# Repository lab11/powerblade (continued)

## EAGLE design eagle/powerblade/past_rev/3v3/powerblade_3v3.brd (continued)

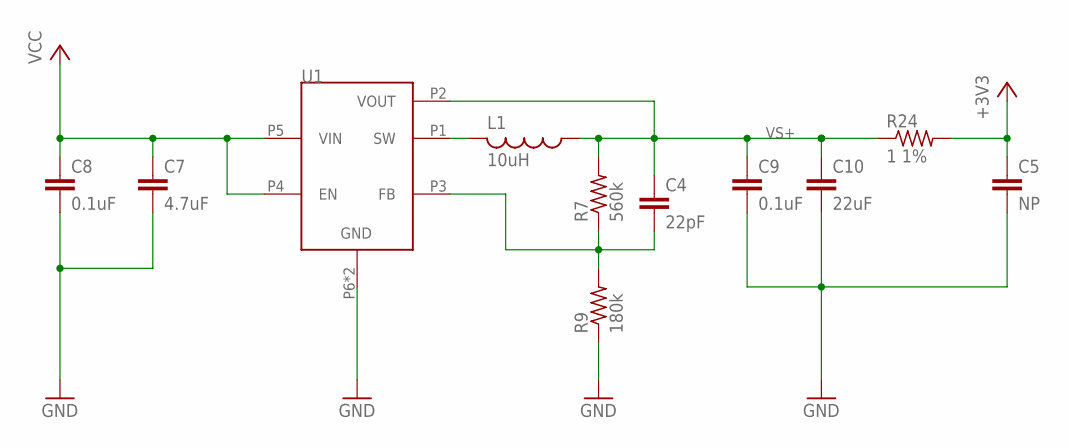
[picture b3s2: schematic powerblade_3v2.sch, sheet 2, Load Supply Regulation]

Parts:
C4: 22pF; C0402; DIGIKEY 445-1239-1-ND
C5: NP; C0603_TN; DIGIKEY NP
C7: 4.7uF; C0402; DIGIKEY 445-8023-1-ND
C8: 0.1uF; C0402; DIGIKEY 445-4952-1-ND
C9: 0.1uF; C0402_SM; DIGIKEY 445-4952-1-ND
C10: 22uF; C0603_SM; DIGIKEY 445-9077-1-ND
L1: 10uH; L0805; DIGIKEY 490-4990-1-ND
R7: 560k; R0402; DIGIKEY P560KLCT-ND
R9: 180k; R0402; DIGIKEY P180KLCT-ND
R24: 1 1%; R0603_SM; DIGIKEY P1.0AJCT-ND
U1: TPS62122; WDFN-6

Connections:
+3V3: C5.1, R24.2; also elsewhere on the board
unnamed: L1.2, U1.P1 (SW)
unnamed: C4.2, R7.1, R9.2, U1.P3 (FB)
VCC: C7.1, C8.1, U1.P4 (EN), U1.P5 (VIN); also elsewhere on the board
VS+: C4.1, C9.1, C10.1, L1.1, R7.2, R24.1, U1.P2 (VOUT); also elsewhere on the board

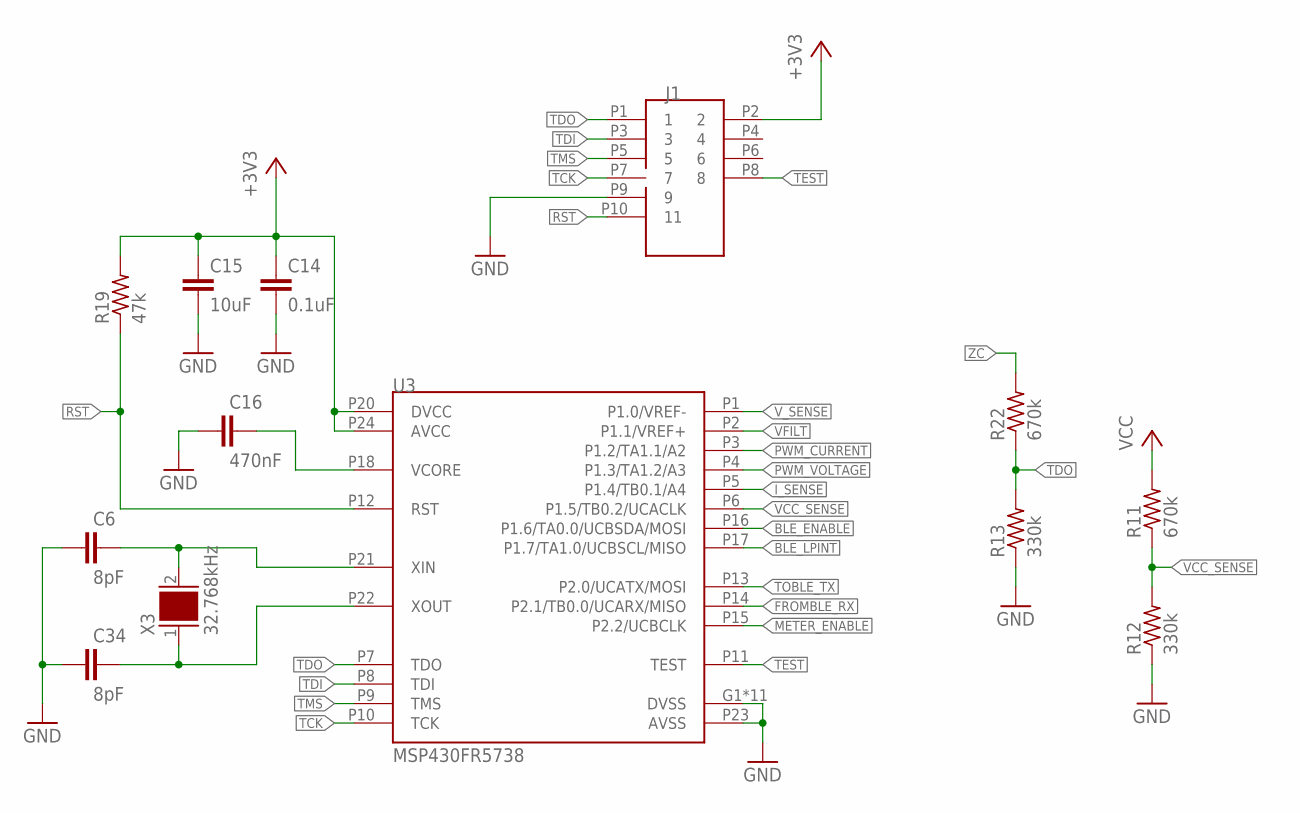
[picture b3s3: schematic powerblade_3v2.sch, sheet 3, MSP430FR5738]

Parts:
C6, C34: 8pF; C0402; DIGIKEY 445-4890-1-ND
C14: 0.1uF; C0402; DIGIKEY 445-4952-1-ND
C15: 10uF; C0603_SM; DIGIKEY 445-6853-1-ND
C16: 470nF; C0402; DIGIKEY 445-4989-1-ND
J1: JTAG_14PIN_IDC-ND; TC2050-IDC-NL-430-ND; DIGIKEY NP
R11, R22: 670k; R0402; DIGIKEY P665KLCT-ND
R12, R13: 330k; R0402; DIGIKEY P330KLCT-ND
R19: 47k; R0402; DIGIKEY P47KJCT-ND
U3: MSP430FR5738; VQFN-24
X3: 32.768kHz; 0805; DIGIKEY 535-12373-1-ND

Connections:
+3V3: C14.1, C15.1, J1.P2 (2), R19.2, U3.P20 (DVCC), U3.P24 (AVCC); also elsewhere on the board
BLE_ENABLE: U3.P16 (P1.6/TA0.0/UCBSDA/MOSI); also elsewhere on the board
BLE_LPINT: U3.P17 (P1.7/TA1.0/UCBSCL/MISO); also elsewhere on the board
FROMBLE_RX: U3.P14 (P2.1/TB0.0/UCARX/MISO); also elsewhere on the board
METER_ENABLE: U3.P15 (P2.2/UCBCLK); also elsewhere on the board
unnamed: C34.2, U3.P22 (XOUT), X3.1
unnamed: C16.2, U3.P18 (VCORE)
unnamed: C6.2, U3.P21 (XIN), X3.2
PWM_CURRENT: U3.P3 (P1.2/TA1.1/A2); also elsewhere on the board
PWM_VOLTAGE: U3.P4 (P1.3/TA1.2/A3); also elsewhere on the board
RST: J1.P10 (11), R19.1, U3.P12 (RST)
TCK: J1.P7 (7), U3.P10 (TCK)
TDI: J1.P3 (3), U3.P8 (TDI)
TDO: J1.P1 (1), R13.2, R22.1, U3.P7 (TDO)
TEST: J1.P8 (8), U3.P11 (TEST)
TMS: J1.P5 (5), U3.P9 (TMS)
TOBLE_TX: U3.P13 (P2.0/UCATX/MOSI); also elsewhere on the board
VCC: R11.2; also elsewhere on the board
VCC_SENSE: R11.1, R12.2, U3.P6 (P1.5/TB0.2/UCACLK)
VFILT: U3.P2 (P1.1/VREF+); also elsewhere on the board
ZC: R22.2; also elsewhere on the board

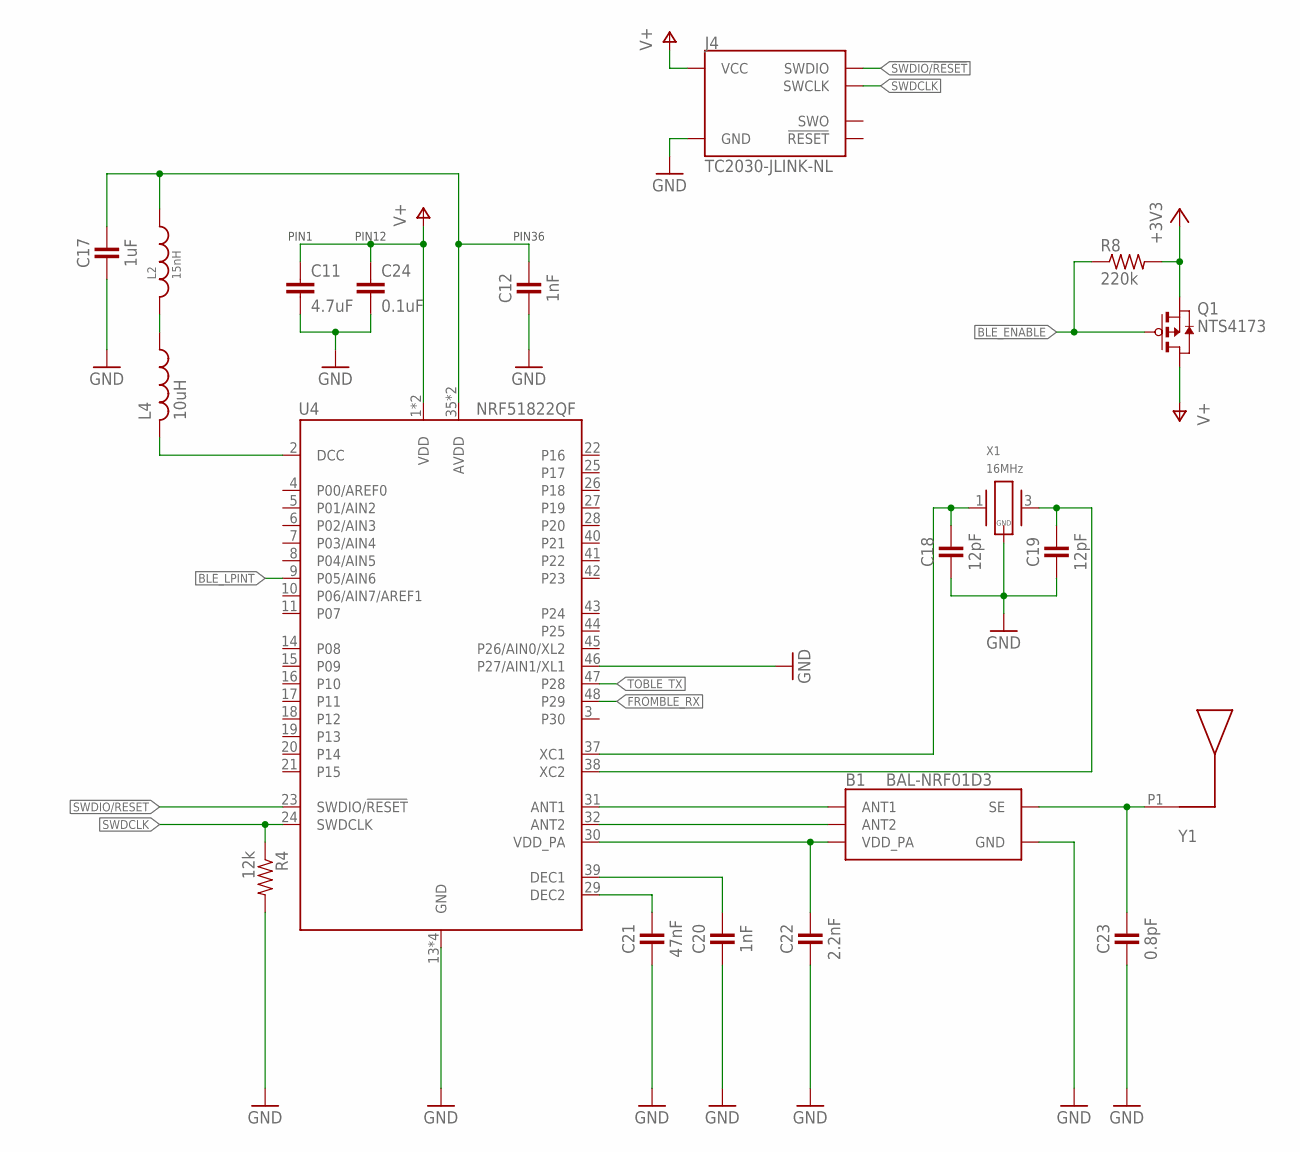
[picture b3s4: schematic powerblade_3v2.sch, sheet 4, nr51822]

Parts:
B1: BAL-NRF01D3
C11: 4.7uF; C0402; DIGIKEY 445-5947-1-ND
C12, C20: 1nF; 0402_CAP; DIGIKEY 490-1303-1-ND
C17: 1uF; 0402_CAP; DIGIKEY 1276-1513-1-ND
C18, C19: 12pF; 0402_CAP; DIGIKEY 490-6197-1-ND
C21: 47nF; 0402_CAP; DIGIKEY 445-1264-1-ND
C22: 2.2nF; 0402_CAP; DIGIKEY 490-5419-1-ND
C23: 0.8pF; 0402_CAP; DIGIKEY 490-6269-1-ND
C24: 0.1uF; C0402; DIGIKEY 445-4952-1-ND
J4: TC2030-JLINK-NL; TC2030-IDC-NL; DIGIKEY NP
L2: 15nH; 0402_CAP; DIGIKEY 587-1521-1-ND
L4: 10uH; C0603_TN; DIGIKEY 490-4025-1-ND
Q1: NTS4173; SC-70-3
R4: 12k; 0402_RES; DIGIKEY RHM12.0KCDCT-ND
R8: 220k; R0402_SM; DIGIKEY P220KJCT-ND
U4: NRF51822QF; QFN-48-6MM
X1: 16MHz; TXC-8Y; DIGIKEY 887-2003-1-ND
Y1: UREACH_XTEND

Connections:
+3V3: Q1.P2 (S), R8.2; also elsewhere on the board
AVDD: C12.1, C17.1, L2.1, U4.35 (AVDD), U4.36 (AVDD)
BLE_ENABLE: Q1.P1 (G), R8.1; also elsewhere on the board
BLE_LPINT: U4.9 (P05/AIN6); also elsewhere on the board
DCC: L4.2, U4.2 (DCC)
FROMBLE_RX: U4.48 (P29); also elsewhere on the board
unnamed: B1.SE, C23.1, Y1.P1
unnamed: B1.ANT1, U4.31 (ANT1)
unnamed: B1.ANT2, U4.32 (ANT2)
unnamed: L2.2, L4.1
unnamed: C18.1, U4.37 (XC1), X1.1
unnamed: C19.1, U4.38 (XC2), X1.3 (2)
unnamed: C20.1, U4.39 (DEC1)
unnamed: C21.1, U4.29 (DEC2)
SWDCLK: J4.4 (SWCLK), R4.1, U4.24 (SWDCLK)
SWDIO/!RESET: J4.2 (SWDIO), U4.23 (SWDIO/!RESET)
TOBLE_TX: U4.47 (P28); also elsewhere on the board
V+: C11.1, C24.1, J4.1 (VCC), Q1.P3 (D), U4.1 (VDD), U4.12 (VDD)
VDD_PA: B1.VCC (VDD_PA), C22.1, U4.30 (VDD_PA)

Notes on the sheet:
PIN12
PIN1
PIN36

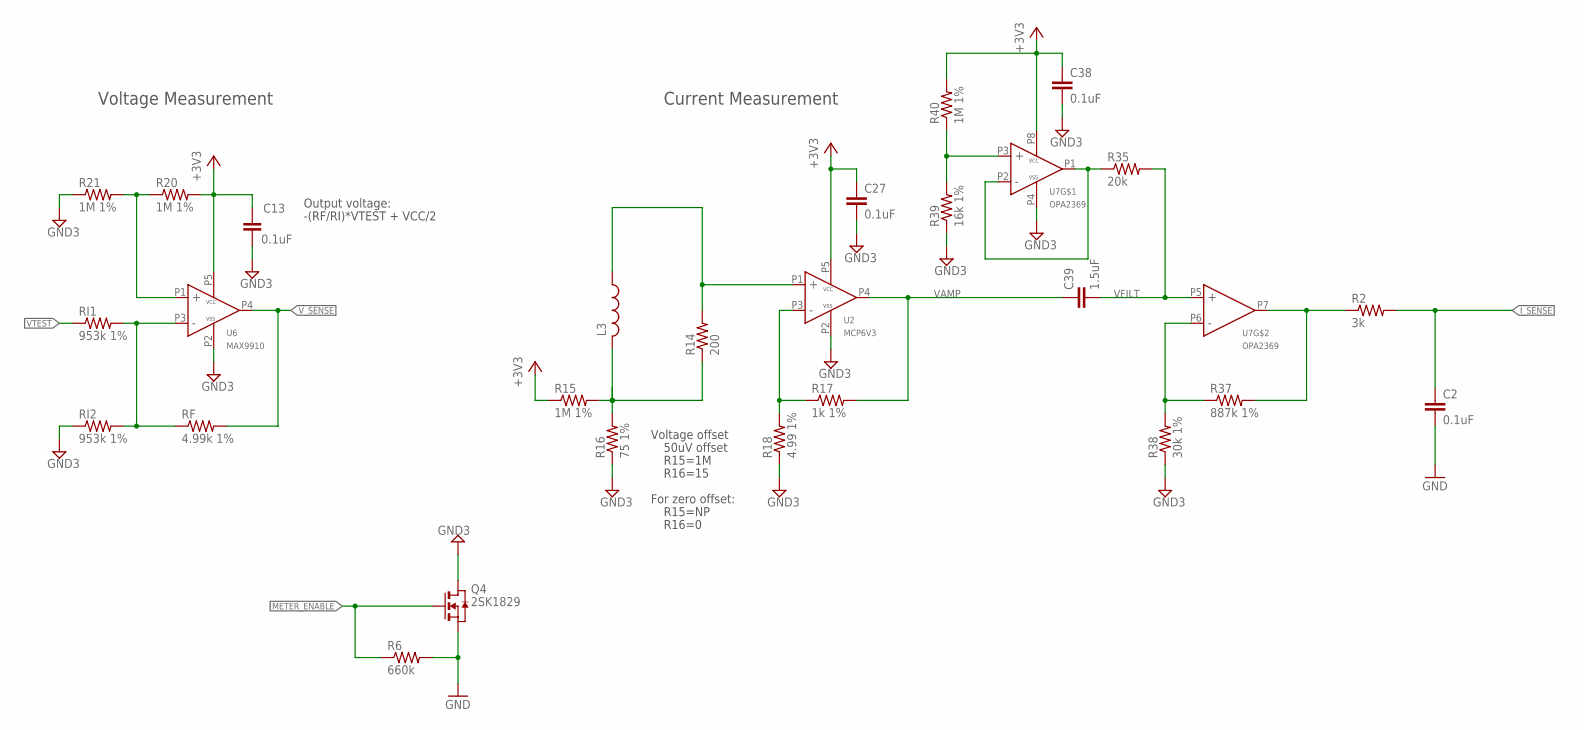
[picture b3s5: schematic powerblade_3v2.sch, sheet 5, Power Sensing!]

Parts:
C2: 0.1uF; C0402; DIGIKEY 490-10777-1-ND
C13: 0.1uF; 0402_CAP; DIGIKEY 445-4952-1-ND
C27, C38: 0.1uF; C0402; DIGIKEY 445-4952-1-ND
C39: 1.5uF; C0402; DIGIKEY 445-13815-1-ND
L3: L-USL0805; L0805; DIGIKEY 732-3452-1-ND
Q4: 2SK1829; SC-70-3
R2: 3k; R0402_SM; DIGIKEY P3.00KLCT-ND
R6: 660k; R0402; DIGIKEY P665KLCT-ND
R14: 200; R0402; DIGIKEY P200LCT-ND
R15, R20, R40: 1M 1%; R0402; DIGIKEY P1.00MLCT-ND
R16: 75 1%; R0402; DIGIKEY P75.0LCT-ND
R17: 1k 1%; R0402; DIGIKEY P1.00KLCT-ND
R18: 4.99 1%; R0402; DIGIKEY RMCF0402FT4R99CT-ND
R21: 1M 1%; R0402_SM; DIGIKEY P1.00MLCT-ND
R35: 20k; R0402; DIGIKEY P20.0KLCT-ND
R37: 887k 1%; R0402; DIGIKEY P887KLCT-ND
R38: 30k 1%; R0402; DIGIKEY P30.0KLCT-ND
R39: 16k 1%; R0402; DIGIKEY P16.0KLCT-ND
RF: 4.99k 1%; R0402; DIGIKEY P4.99KLCT-ND
RI1, RI2: 953k 1%; R0402; DIGIKEY P953KLCT-ND
U2: MCP6V3; SC70-5; DIGIKEY 296-19547-1-ND
U6: MAX9910; SC70-5; DIGIKEY 296-25252-1-ND
U7: OPA2369; SOT-23-8

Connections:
+3V3: C13.1, C27.1, C38.1, R15.1, R20.2, R40.2, U2.P5 (VCC), U6.P5 (VCC), U7.P8 (VCC); also elsewhere on the board
METER_ENABLE: Q4.P1 (G), R6.1; also elsewhere on the board
unnamed: R2.1, R37.2, U7.P7 (OUT)
unnamed 20: L3.2, R14.1, R15.2, R16.2; also elsewhere on the board
unnamed: L3.1, R14.2, U2.P1 (IN+)
unnamed: R20.1, R21.2, U6.P1 (IN+)
unnamed: RF.1, RI1.2, RI2.2, U6.P3 (IN-)
unnamed 25: R17.1, R18.2, U2.P3 (IN-); also elsewhere on the board
unnamed: R37.1, R38.2, U7.P6 (IN-)
unnamed: R35.1, U7.P1 (OUT), U7.P2 (IN-)
unnamed: R39.2, R40.1, U7.P3 (IN+)
VAMP: C39.1, R17.2, U2.P4 (OUT)
VFILT: C39.2, R35.2, U7.P5 (IN+); also elsewhere on the board
VTEST: RI1.1; also elsewhere on the board

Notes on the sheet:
Voltage offset
50uV offset
For zero offset:
R15=NP
R16=0
Current Measurement
Voltage Measurement
Output voltage:
-(RF/RI)*VTEST + VCC/2
R15=1M
R16=15

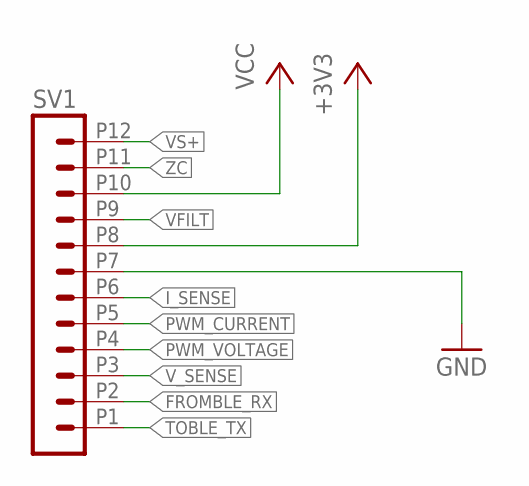
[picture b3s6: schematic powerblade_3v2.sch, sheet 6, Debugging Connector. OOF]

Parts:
SV1: MA12-11M27; MA12-1_1MM27; DIGIKEY S9014E-12-ND

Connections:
+3V3: SV1.P8 (8); also elsewhere on the board
FROMBLE_RX: SV1.P2 (2); also elsewhere on the board
PWM_CURRENT: SV1.P5 (5); also elsewhere on the board
PWM_VOLTAGE: SV1.P4 (4); also elsewhere on the board
TOBLE_TX: SV1.P1 (1); also elsewhere on the board
VCC: SV1.P10 (10); also elsewhere on the board
VFILT: SV1.P9 (9); also elsewhere on the board
VS+: SV1.P12 (12); also elsewhere on the board
ZC: SV1.P11 (11); also elsewhere on the board

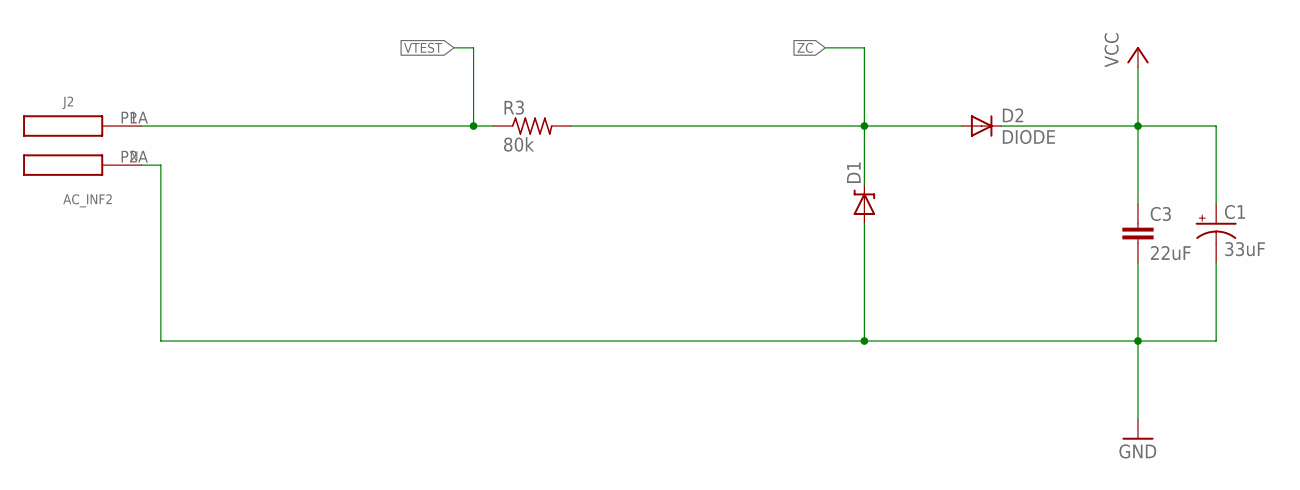
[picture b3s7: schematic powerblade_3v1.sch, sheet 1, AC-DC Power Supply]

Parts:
C1: 33uF; CPOL0805_SM; DIGIKEY 478-8650-1-ND
C3: 22uF; C0603_SM; DIGIKEY 445-9077-1-ND
D1: ZENERBZT52; BZT52; DIGIKEY BZT52C10T-7DICT-ND
D2: DIODE; BAS521
J2: AC_INF2; AC3_F2; DIGIKEY NP
R3: 80k; R1210; DIGIKEY P80.6KAACT-ND

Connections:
VCC: C1.+, C3.1, D2.C; also elsewhere on the board
VTEST: J2.P1A, R3.1; also elsewhere on the board
ZC: D1.C, D2.A, R3.2; also elsewhere on the board

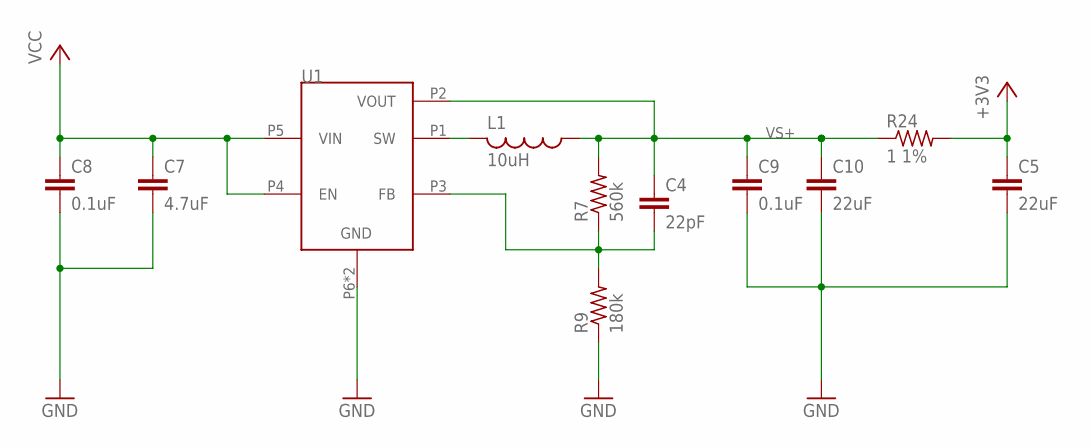
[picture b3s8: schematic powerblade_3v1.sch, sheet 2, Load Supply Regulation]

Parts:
C4: 22pF; C0402_SM; DIGIKEY 445-1239-1-ND
C5: 22uF; C0603_TN; DIGIKEY 445-9077-1-ND
C7: 4.7uF; C0402_SM; DIGIKEY 445-8023-1-ND
C8, C9: 0.1uF; C0402_SM; DIGIKEY 445-4952-1-ND
C10: 22uF; C0603_SM; DIGIKEY 445-9077-1-ND
L1: 10uH; L0805; DIGIKEY 490-4990-1-ND
R7: 560k; R0402_SM; DIGIKEY P560KLCT-ND
R9: 180k; R0402_SM; DIGIKEY P180KLCT-ND
R24: 1 1%; R0603_SM; DIGIKEY P1.0AJCT-ND
U1: TPS62122; WDFN-6

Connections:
+3V3: C5.1, R24.2; also elsewhere on the board
unnamed: L1.2, U1.P1 (SW)
unnamed: C4.2, R7.1, R9.2, U1.P3 (FB)
VCC: C7.1, C8.1, U1.P4 (EN), U1.P5 (VIN); also elsewhere on the board
VS+: C4.1, C9.1, C10.1, L1.1, R7.2, R24.1, U1.P2 (VOUT); also elsewhere on the board

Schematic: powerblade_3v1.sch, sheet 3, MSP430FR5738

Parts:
C6, C34: 8pF; C0402_SM; DIGIKEY 445-4890-1-ND
C14: 0.1uF; C0402_SM; DIGIKEY 445-4952-1-ND
C15: 10uF; C0603_SM; DIGIKEY 445-6853-1-ND
C16: 470nF; C0402_SM; DIGIKEY 445-4989-1-ND
J1: JTAG_14PIN_IDC-ND; TC2050-IDC-NL-430-ND; DIGIKEY NP
R11, R22: 670k; R0402_SM; DIGIKEY P665KLCT-ND
R12, R13: 330k; R0402_SM; DIGIKEY P330KLCT-ND
R19: 47k; R0402_SM; DIGIKEY P47KJCT-ND
U3: MSP430FR5738; VQFN-24
X3: 32.768kHz; 0805; DIGIKEY 535-12373-1-ND

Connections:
+3V3: C14.1, C15.1, J1.P2 (2), R19.2, U3.P20 (DVCC), U3.P24 (AVCC); also elsewhere on the board
BLE_ENABLE: U3.P16 (P1.6/TA0.0/UCBSDA/MOSI); also elsewhere on the board
BLE_LPINT: U3.P17 (P1.7/TA1.0/UCBSCL/MISO); also elsewhere on the board
FROMBLE_RX: U3.P14 (P2.1/TB0.0/UCARX/MISO); also elsewhere on the board
METER_ENABLE: U3.P15 (P2.2/UCBCLK); also elsewhere on the board
unnamed: C34.2, U3.P22 (XOUT), X3.1
unnamed: C16.2, U3.P18 (VCORE)
unnamed: C6.2, U3.P21 (XIN), X3.2
PWM_CURRENT: U3.P3 (P1.2/TA1.1/A2); also elsewhere on the board
PWM_VOLTAGE: U3.P4 (P1.3/TA1.2/A3); also elsewhere on the board
RST: J1.P10 (11), R19.1, U3.P12 (RST)
TCK: J1.P7 (7), U3.P10 (TCK)
TDI: J1.P3 (3), U3.P8 (TDI)
TDO: J1.P1 (1), R13.2, R22.1, U3.P7 (TDO)
TEST: J1.P8 (8), U3.P11 (TEST)
TMS: J1.P5 (5), U3.P9 (TMS)
TOBLE_TX: U3.P13 (P2.0/UCATX/MOSI); also elsewhere on the board
VCC: R11.2; also elsewhere on the board
VCC_SENSE: R11.1, R12.2, U3.P6 (P1.5/TB0.2/UCACLK)
VFILT: U3.P2 (P1.1/VREF+); also elsewhere on the board
ZC: R22.2; also elsewhere on the board

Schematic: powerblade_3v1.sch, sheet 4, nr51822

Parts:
B1: BAL-NRF01D3
C11: 4.7uF; C0402_SM; DIGIKEY 445-5947-1-ND
C12, C20: 1nF; 0402_CAP; DIGIKEY 490-1303-1-ND
C17: 1uF; 0402_CAP; DIGIKEY 1276-1513-1-ND
C18, C19: 12pF; 0402_CAP; DIGIKEY 490-6197-1-ND
C21: 47nF; 0402_CAP; DIGIKEY 445-1264-1-ND
C22: 2.2nF; 0402_CAP; DIGIKEY 490-5419-1-ND
C23: 0.8pF; 0402_CAP; DIGIKEY 490-6269-1-ND
C24: 0.1uF; C0402_SM; DIGIKEY 445-4952-1-ND
J4: TC2030-JLINK-NL; TC2030-IDC-NL; DIGIKEY NP
L2: 15nH; 0402_CAP; DIGIKEY 587-1521-1-ND
L4: 10uH; C0603_TN; DIGIKEY 490-4025-1-ND
Q1: NTS4173; SC-70-3
R4: 12k; 0402_RES; DIGIKEY RHM12.0KCDCT-ND
R8: 220k; R0402_SM; DIGIKEY P220KJCT-ND
U4: NRF51822QF; QFN-48-6MM
X1: 16MHz; TXC-8Y; DIGIKEY 887-2003-1-ND
Y1: UREACH_XTEND

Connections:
+3V3: Q1.P2 (S), R8.2; also elsewhere on the board
AVDD: C12.1, C17.1, L2.1, U4.35 (AVDD), U4.36 (AVDD)
BLE_ENABLE: Q1.P1 (G), R8.1; also elsewhere on the board
BLE_LPINT: U4.9 (P05/AIN6); also elsewhere on the board
DCC: L4.2, U4.2 (DCC)
FROMBLE_RX: U4.48 (P29); also elsewhere on the board
unnamed: B1.SE, C23.1, Y1.P1
unnamed: B1.ANT1, U4.31 (ANT1)
unnamed: B1.ANT2, U4.32 (ANT2)
unnamed: L2.2, L4.1
unnamed: C18.1, U4.37 (XC1), X1.1
unnamed: C19.1, U4.38 (XC2), X1.3 (2)
unnamed: C20.1, U4.39 (DEC1)
unnamed: C21.1, U4.29 (DEC2)
SWDCLK: J4.4 (SWCLK), R4.1, U4.24 (SWDCLK)
SWDIO/!RESET: J4.2 (SWDIO), U4.23 (SWDIO/!RESET)
TOBLE_TX: U4.47 (P28); also elsewhere on the board
V+: C11.1, C24.1, J4.1 (VCC), Q1.P3 (D), U4.1 (VDD), U4.12 (VDD)
VDD_PA: B1.VCC (VDD_PA), C22.1, U4.30 (VDD_PA)

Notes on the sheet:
PIN12
PIN1
PIN36

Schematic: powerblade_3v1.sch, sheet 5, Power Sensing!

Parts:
C2: C-EUC0402_SM; C0402_SM
C13: 0.1uF; 0402_CAP; DIGIKEY 445-4952-1-ND
C27, C38: 0.1uF; C0402_SM; DIGIKEY 445-4952-1-ND
C39: 1.5uF; C0402_SM; DIGIKEY 445-13815-1-ND
L3: L-USL0805; L0805; DIGIKEY 732-3452-1-ND
Q4: 2SK1829; SC-70-3
R1: NP; R0402_SM; DIGIKEY NP
R2: R-US_R0402_SM; R0402_SM
R6: 660k; R0402_SM; DIGIKEY P665KLCT-ND
R14: 200; R0402_SM; DIGIKEY P200LCT-ND
R15, R20, R21, R40: 1M 1%; R0402_SM; DIGIKEY P1.00MLCT-ND
R16: 75 1%; R0402_SM; DIGIKEY P75.0LCT-ND
R17: 4.99k 1%; R0402_SM; DIGIKEY P4.99KLCT-ND
R18: 4.99 1%; R0402_SM; DIGIKEY RMCF0402FT4R99CT-ND
R35: 20k; R0402_SM; DIGIKEY P2.00KLCT-ND
R37: 887k 1%; R0402_SM; DIGIKEY P887KLCT-ND
R38: 30k 1%; R0402_SM; DIGIKEY P30.0KLCT-ND
R39: 16k 1%; R0402_SM; DIGIKEY P16.0KLCT-ND
RF: 4.99k 1%; R0402_SM; DIGIKEY P4.99KLCT-ND
RI1, RI2: 953k 1%; R0402_SM; DIGIKEY P953KLCT-ND
U2: MCP6V3; SC70-5; DIGIKEY_POP 296-19547-1-ND
U6: MAX9910; SC70-5; DIGIKEY 296-25252-1-ND
U7: OPA2369; SOT-23-8

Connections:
+3V3: C13.1, C27.1, C38.1, R15.1, R20.2, R40.2, U2.P5 (VCC), U6.P5 (VCC), U7.P8 (VCC); also elsewhere on the board
METER_ENABLE: Q4.P1 (G), R6.1; also elsewhere on the board
unnamed: R2.1, R37.2, U7.P7 (OUT)
unnamed: L3.2, R1.1, R14.1, R15.2, R16.2
unnamed: L3.1, R14.2, U2.P1 (IN+)
unnamed: R20.1, R21.2, U6.P1 (IN+)
unnamed: RF.1, RI1.2, RI2.2, U6.P3 (IN-)
unnamed: R1.2, R17.1, R18.2, U2.P3 (IN-)
unnamed: R37.1, R38.2, U7.P6 (IN-)
unnamed: R35.1, U7.P1 (OUT), U7.P2 (IN-)
unnamed: R39.2, R40.1, U7.P3 (IN+)
VAMP: C39.1, R17.2, U2.P4 (OUT)
VFILT: C39.2, R35.2, U7.P5 (IN+); also elsewhere on the board
VTEST: RI1.1; also elsewhere on the board

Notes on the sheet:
Voltage offset
50uV offset
For zero offset:
R15=NP
R16=0
Current Measurement
Voltage Measurement
Output voltage:
-(RF/RI)*VTEST + VCC/2
R15=1M
R16=15

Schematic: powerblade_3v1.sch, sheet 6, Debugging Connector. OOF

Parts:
SV1: MA12-11M27; MA12-1_1MM27; DIGIKEY S9014E-12-ND

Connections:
+3V3: SV1.P8 (8); also elsewhere on the board
FROMBLE_RX: SV1.P2 (2); also elsewhere on the board
PWM_CURRENT: SV1.P5 (5); also elsewhere on the board
PWM_VOLTAGE: SV1.P4 (4); also elsewhere on the board
TOBLE_TX: SV1.P1 (1); also elsewhere on the board
VCC: SV1.P10 (10); also elsewhere on the board
VFILT: SV1.P9 (9); also elsewhere on the board
VS+: SV1.P12 (12); also elsewhere on the board
ZC: SV1.P11 (11); also elsewhere on the board

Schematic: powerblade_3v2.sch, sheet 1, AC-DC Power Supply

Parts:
C1: 33uF; CPOL0805_SM; DIGIKEY 478-8650-1-ND
C3: 22uF; C0603_SM; DIGIKEY 445-9077-1-ND
D1: ZENERBZT52; BZT52; DIGIKEY BZT52C10T-7DICT-ND
D2: DIODE; BAS521
J2: AC_INF45; AC3_F45; DIGIKEY ED1649-ND
R3: 69.8k; R1210; DIGIKEY P69.8KAACT-ND

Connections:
VCC: C1.+, C3.1, D2.C; also elsewhere on the board
VTEST: J2.PA.3, R3.1; also elsewhere on the board
ZC: D1.C, D2.A, R3.2; also elsewhere on the board

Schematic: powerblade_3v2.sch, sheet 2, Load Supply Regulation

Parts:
C4: 22pF; C0402; DIGIKEY 445-1239-1-ND
C5: NP; C0603_TN; DIGIKEY NP
C7: 4.7uF; C0402; DIGIKEY 445-8023-1-ND
C8: 0.1uF; C0402; DIGIKEY 445-4952-1-ND
C9: 0.1uF; C0402_SM; DIGIKEY 445-4952-1-ND
C10: 22uF; C0603_SM; DIGIKEY 445-9077-1-ND
L1: 10uH; L0805; DIGIKEY 490-4990-1-ND
R7: 560k; R0402; DIGIKEY P560KLCT-ND
R9: 180k; R0402; DIGIKEY P180KLCT-ND
R24: 1 1%; R0603_SM; DIGIKEY P1.0AJCT-ND
U1: TPS62122; WDFN-6

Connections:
+3V3: C5.1, R24.2; also elsewhere on the board
unnamed: L1.2, U1.P1 (SW)
unnamed: C4.2, R7.1, R9.2, U1.P3 (FB)
VCC: C7.1, C8.1, U1.P4 (EN), U1.P5 (VIN); also elsewhere on the board
VS+: C4.1, C9.1, C10.1, L1.1, R7.2, R24.1, U1.P2 (VOUT); also elsewhere on the board

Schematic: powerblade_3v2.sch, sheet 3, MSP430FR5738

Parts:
C6, C34: 8pF; C0402; DIGIKEY 445-4890-1-ND
C14: 0.1uF; C0402; DIGIKEY 445-4952-1-ND
C15: 10uF; C0603_SM; DIGIKEY 445-6853-1-ND
C16: 470nF; C0402; DIGIKEY 445-4989-1-ND
J1: JTAG_14PIN_IDC-ND; TC2050-IDC-NL-430-ND; DIGIKEY NP
R11, R22: 670k; R0402; DIGIKEY P665KLCT-ND
R12, R13: 330k; R0402; DIGIKEY P330KLCT-ND
R19: 47k; R0402; DIGIKEY P47KJCT-ND
U3: MSP430FR5738; VQFN-24
X3: 32.768kHz; 0805; DIGIKEY 535-12373-1-ND

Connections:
+3V3: C14.1, C15.1, J1.P2 (2), R19.2, U3.P20 (DVCC), U3.P24 (AVCC); also elsewhere on the board
BLE_ENABLE: U3.P16 (P1.6/TA0.0/UCBSDA/MOSI); also elsewhere on the board
BLE_LPINT: U3.P17 (P1.7/TA1.0/UCBSCL/MISO); also elsewhere on the board
FROMBLE_RX: U3.P14 (P2.1/TB0.0/UCARX/MISO); also elsewhere on the board
METER_ENABLE: U3.P15 (P2.2/UCBCLK); also elsewhere on the board
unnamed: C34.2, U3.P22 (XOUT), X3.1
unnamed: C16.2, U3.P18 (VCORE)
unnamed: C6.2, U3.P21 (XIN), X3.2
PWM_CURRENT: U3.P3 (P1.2/TA1.1/A2); also elsewhere on the board
PWM_VOLTAGE: U3.P4 (P1.3/TA1.2/A3); also elsewhere on the board
RST: J1.P10 (11), R19.1, U3.P12 (RST)
TCK: J1.P7 (7), U3.P10 (TCK)
TDI: J1.P3 (3), U3.P8 (TDI)
TDO: J1.P1 (1), R13.2, R22.1, U3.P7 (TDO)
TEST: J1.P8 (8), U3.P11 (TEST)
TMS: J1.P5 (5), U3.P9 (TMS)
TOBLE_TX: U3.P13 (P2.0/UCATX/MOSI); also elsewhere on the board
VCC: R11.2; also elsewhere on the board
VCC_SENSE: R11.1, R12.2, U3.P6 (P1.5/TB0.2/UCACLK)
VFILT: U3.P2 (P1.1/VREF+); also elsewhere on the board
ZC: R22.2; also elsewhere on the board

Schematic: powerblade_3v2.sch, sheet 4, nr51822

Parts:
B1: BAL-NRF01D3
C11: 4.7uF; C0402; DIGIKEY 445-5947-1-ND
C12, C20: 1nF; 0402_CAP; DIGIKEY 490-1303-1-ND
C17: 1uF; 0402_CAP; DIGIKEY 1276-1513-1-ND
C18, C19: 12pF; 0402_CAP; DIGIKEY 490-6197-1-ND
C21: 47nF; 0402_CAP; DIGIKEY 445-1264-1-ND
C22: 2.2nF; 0402_CAP; DIGIKEY 490-5419-1-ND
C23: 0.8pF; 0402_CAP; DIGIKEY 490-6269-1-ND
C24: 0.1uF; C0402; DIGIKEY 445-4952-1-ND
J4: TC2030-JLINK-NL; TC2030-IDC-NL; DIGIKEY NP
L2: 15nH; 0402_CAP; DIGIKEY 587-1521-1-ND
L4: 10uH; C0603_TN; DIGIKEY 490-4025-1-ND
Q1: NTS4173; SC-70-3
R4: 12k; 0402_RES; DIGIKEY RHM12.0KCDCT-ND
R8: 220k; R0402_SM; DIGIKEY P220KJCT-ND
U4: NRF51822QF; QFN-48-6MM
X1: 16MHz; TXC-8Y; DIGIKEY 887-2003-1-ND
Y1: UREACH_XTEND

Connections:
+3V3: Q1.P2 (S), R8.2; also elsewhere on the board
AVDD: C12.1, C17.1, L2.1, U4.35 (AVDD), U4.36 (AVDD)
BLE_ENABLE: Q1.P1 (G), R8.1; also elsewhere on the board
BLE_LPINT: U4.9 (P05/AIN6); also elsewhere on the board
DCC: L4.2, U4.2 (DCC)
FROMBLE_RX: U4.48 (P29); also elsewhere on the board
unnamed: B1.SE, C23.1, Y1.P1
unnamed: B1.ANT1, U4.31 (ANT1)
unnamed: B1.ANT2, U4.32 (ANT2)
unnamed: L2.2, L4.1
unnamed: C18.1, U4.37 (XC1), X1.1
unnamed: C19.1, U4.38 (XC2), X1.3 (2)
unnamed: C20.1, U4.39 (DEC1)
unnamed: C21.1, U4.29 (DEC2)
SWDCLK: J4.4 (SWCLK), R4.1, U4.24 (SWDCLK)
SWDIO/!RESET: J4.2 (SWDIO), U4.23 (SWDIO/!RESET)
TOBLE_TX: U4.47 (P28); also elsewhere on the board
V+: C11.1, C24.1, J4.1 (VCC), Q1.P3 (D), U4.1 (VDD), U4.12 (VDD)
VDD_PA: B1.VCC (VDD_PA), C22.1, U4.30 (VDD_PA)

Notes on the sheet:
PIN12
PIN1
PIN36

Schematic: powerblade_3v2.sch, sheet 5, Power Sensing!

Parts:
C2: 0.1uF; C0402; DIGIKEY 490-10777-1-ND
C13: 0.1uF; 0402_CAP; DIGIKEY 445-4952-1-ND
C27, C38: 0.1uF; C0402; DIGIKEY 445-4952-1-ND
C39: 1.5uF; C0402; DIGIKEY 445-13815-1-ND
L3: L-USL0805; L0805; DIGIKEY 732-3452-1-ND
Q4: 2SK1829; SC-70-3
R2: 3k; R0402_SM; DIGIKEY P3.00KLCT-ND
R6: 660k; R0402; DIGIKEY P665KLCT-ND
R14: 200; R0402; DIGIKEY P200LCT-ND
R15, R20, R40: 1M 1%; R0402; DIGIKEY P1.00MLCT-ND
R16: 75 1%; R0402; DIGIKEY P75.0LCT-ND
R17: 1k 1%; R0402; DIGIKEY P1.00KLCT-ND
R18: 4.99 1%; R0402; DIGIKEY RMCF0402FT4R99CT-ND
R21: 1M 1%; R0402_SM; DIGIKEY P1.00MLCT-ND
R35: 20k; R0402; DIGIKEY P20.0KLCT-ND
R37: 887k 1%; R0402; DIGIKEY P887KLCT-ND
R38: 30k 1%; R0402; DIGIKEY P30.0KLCT-ND
R39: 16k 1%; R0402; DIGIKEY P16.0KLCT-ND
RF: 4.99k 1%; R0402; DIGIKEY P4.99KLCT-ND
RI1, RI2: 953k 1%; R0402; DIGIKEY P953KLCT-ND
U2: MCP6V3; SC70-5; DIGIKEY 296-19547-1-ND
U6: MAX9910; SC70-5; DIGIKEY 296-25252-1-ND
U7: OPA2369; SOT-23-8

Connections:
+3V3: C13.1, C27.1, C38.1, R15.1, R20.2, R40.2, U2.P5 (VCC), U6.P5 (VCC), U7.P8 (VCC); also elsewhere on the board
METER_ENABLE: Q4.P1 (G), R6.1; also elsewhere on the board
unnamed: R2.1, R37.2, U7.P7 (OUT)
unnamed 20: L3.2, R14.1, R15.2, R16.2; also elsewhere on the board
unnamed: L3.1, R14.2, U2.P1 (IN+)
unnamed: R20.1, R21.2, U6.P1 (IN+)
unnamed: RF.1, RI1.2, RI2.2, U6.P3 (IN-)
unnamed 25: R17.1, R18.2, U2.P3 (IN-); also elsewhere on the board
unnamed: R37.1, R38.2, U7.P6 (IN-)
unnamed: R35.1, U7.P1 (OUT), U7.P2 (IN-)
unnamed: R39.2, R40.1, U7.P3 (IN+)
VAMP: C39.1, R17.2, U2.P4 (OUT)
VFILT: C39.2, R35.2, U7.P5 (IN+); also elsewhere on the board
VTEST: RI1.1; also elsewhere on the board

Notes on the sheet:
Voltage offset
50uV offset
For zero offset:
R15=NP
R16=0
Current Measurement
Voltage Measurement
Output voltage:
-(RF/RI)*VTEST + VCC/2
R15=1M
R16=15

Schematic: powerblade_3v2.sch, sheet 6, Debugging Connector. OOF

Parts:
SV1: MA12-11M27; MA12-1_1MM27; DIGIKEY S9014E-12-ND

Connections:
+3V3: SV1.P8 (8); also elsewhere on the board
FROMBLE_RX: SV1.P2 (2); also elsewhere on the board
PWM_CURRENT: SV1.P5 (5); also elsewhere on the board
PWM_VOLTAGE: SV1.P4 (4); also elsewhere on the board
TOBLE_TX: SV1.P1 (1); also elsewhere on the board
VCC: SV1.P10 (10); also elsewhere on the board
VFILT: SV1.P9 (9); also elsewhere on the board
VS+: SV1.P12 (12); also elsewhere on the board
ZC: SV1.P11 (11); also elsewhere on the board

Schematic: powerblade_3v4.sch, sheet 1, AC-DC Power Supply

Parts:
C1: 33uF; CPOL0805_SM; DIGIKEY 478-8650-1-ND
C3: 22uF; C0603_SM; DIGIKEY 445-9077-1-ND
D1: ZENERBZT52; BZT52; DIGIKEY BZT52C10T-7DICT-ND
D2: DIODE; BAS521
J2: AC_INFINAL; AC3_FINAL; DIGIKEY ED1649-ND
R3: 69.8k; R1210; DIGIKEY P69.8KAACT-ND

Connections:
VCC: C1.+, C3.1, D2.C; also elsewhere on the board
VTEST: J2.PA.3, R3.1; also elsewhere on the board
ZC: D1.C, D2.A, R3.2; also elsewhere on the board

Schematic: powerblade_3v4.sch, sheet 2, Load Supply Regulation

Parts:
C4: 22pF; C0402; DIGIKEY 445-1239-1-ND
C5: NP; C0603_TN; DIGIKEY NP
C7: 4.7uF; C0402; DIGIKEY 445-8023-1-ND
C8: 0.1uF; C0402; DIGIKEY 445-4952-1-ND
C9: 0.1uF; C0402_SM; DIGIKEY 445-4952-1-ND
C10: 22uF; C0603_SM; DIGIKEY 445-9077-1-ND
L1: 10uH; L0805; DIGIKEY 490-4990-1-ND
R7: 560k; R0402; DIGIKEY P560KLCT-ND
R9: 180k; R0402; DIGIKEY P180KLCT-ND
R24: 1 1%; R0603_SM; DIGIKEY P1.0AJCT-ND
U1: TPS62122; WDFN-6

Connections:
+3V3: C5.1, R24.2; also elsewhere on the board
unnamed: L1.2, U1.P1 (SW)
unnamed: C4.2, R7.1, R9.2, U1.P3 (FB)
VCC: C7.1, C8.1, U1.P4 (EN), U1.P5 (VIN); also elsewhere on the board
VS+: C4.1, C9.1, C10.1, L1.1, R7.2, R24.1, U1.P2 (VOUT); also elsewhere on the board

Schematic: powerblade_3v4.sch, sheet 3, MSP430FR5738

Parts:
C6, C34: 8pF; C0402; DIGIKEY 445-4890-1-ND
C14: 0.1uF; C0402; DIGIKEY 445-4952-1-ND
C15: 10uF; C0603_SM; DIGIKEY 445-6853-1-ND
C16: 470nF; C0402; DIGIKEY 445-4989-1-ND
J1: JTAG_14PIN_IDC-ND; TC2050-IDC-NL-430-ND; DIGIKEY NP
R11, R22: 670k; R0402; DIGIKEY P665KLCT-ND
R12, R13: 330k; R0402; DIGIKEY P330KLCT-ND
R19: 47k; R0402; DIGIKEY P47KJCT-ND
U3: MSP430FR5738; VQFN-24
X3: 32.768kHz; 0805; DIGIKEY 535-12373-1-ND

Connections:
+3V3: C14.1, C15.1, J1.P2 (2), R19.2, U3.P20 (DVCC), U3.P24 (AVCC); also elsewhere on the board
BLE_ENABLE: U3.P16 (P1.6/TA0.0/UCBSDA/MOSI); also elsewhere on the board
BLE_LPINT: U3.P17 (P1.7/TA1.0/UCBSCL/MISO); also elsewhere on the board
FROMBLE_RX: U3.P14 (P2.1/TB0.0/UCARX/MISO); also elsewhere on the board
METER_ENABLE: U3.P15 (P2.2/UCBCLK); also elsewhere on the board
unnamed: C34.2, U3.P22 (XOUT), X3.1
unnamed: C16.2, U3.P18 (VCORE)
unnamed: C6.2, U3.P21 (XIN), X3.2
PWM_CURRENT: U3.P3 (P1.2/TA1.1/A2); also elsewhere on the board
PWM_VOLTAGE: U3.P4 (P1.3/TA1.2/A3); also elsewhere on the board
RST: J1.P10 (11), R19.1, U3.P12 (RST)
TCK: J1.P7 (7), U3.P10 (TCK)
TDI: J1.P3 (3), U3.P8 (TDI)
TDO: J1.P1 (1), R13.2, R22.1, U3.P7 (TDO)
TEST: J1.P8 (8), U3.P11 (TEST)
TMS: J1.P5 (5), U3.P9 (TMS)
TOBLE_TX: U3.P13 (P2.0/UCATX/MOSI); also elsewhere on the board
VCC: R11.2; also elsewhere on the board
VCC_SENSE: R11.1, R12.2, U3.P6 (P1.5/TB0.2/UCACLK)
VFILT: U3.P2 (P1.1/VREF+); also elsewhere on the board
ZC: R22.2; also elsewhere on the board

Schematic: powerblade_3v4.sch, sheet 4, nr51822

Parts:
B1: BAL-NRF01D3
C11: 4.7uF; C0402; DIGIKEY 445-5947-1-ND
C12, C20: 1nF; 0402_CAP; DIGIKEY 490-1303-1-ND
C17: 1uF; 0402_CAP; DIGIKEY 1276-1513-1-ND
C18, C19: 12pF; 0402_CAP; DIGIKEY 490-6197-1-ND
C21: 47nF; 0402_CAP; DIGIKEY 445-1264-1-ND
C22: 2.2nF; 0402_CAP; DIGIKEY 490-5419-1-ND
C23: 0.8pF; 0402_CAP; DIGIKEY 490-6269-1-ND
C24: 0.1uF; C0402; DIGIKEY 445-4952-1-ND
J4: TC2030-JLINK-NL; TC2030-IDC-NL; DIGIKEY NP
L2: 15nH; 0402_CAP; DIGIKEY 587-1521-1-ND
L4: 10uH; C0603_TN; DIGIKEY 490-4025-1-ND
Q1: NTS4173; SC-70-3
R4: 12k; 0402_RES; DIGIKEY RHM12.0KCDCT-ND
R8: 220k; R0402_SM; DIGIKEY P220KJCT-ND
U4: NRF51822QF; QFN-48-6MM
X1: 16MHz; TXC-8Y; DIGIKEY 887-2003-1-ND
Y1: UREACH_XTEND

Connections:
+3V3: Q1.P2 (S), R8.2; also elsewhere on the board
AVDD: C12.1, C17.1, L2.1, U4.35 (AVDD), U4.36 (AVDD)
BLE_ENABLE: Q1.P1 (G), R8.1; also elsewhere on the board
BLE_LPINT: U4.9 (P05/AIN6); also elsewhere on the board
DCC: L4.2, U4.2 (DCC)
FROMBLE_RX: U4.48 (P29); also elsewhere on the board
unnamed: B1.SE, C23.1, Y1.P1
unnamed: B1.ANT1, U4.31 (ANT1)
unnamed: B1.ANT2, U4.32 (ANT2)
unnamed: L2.2, L4.1
unnamed: C18.1, U4.37 (XC1), X1.1
unnamed: C19.1, U4.38 (XC2), X1.3 (2)
unnamed: C20.1, U4.39 (DEC1)
unnamed: C21.1, U4.29 (DEC2)
SWDCLK: J4.4 (SWCLK), R4.1, U4.24 (SWDCLK)
SWDIO/!RESET: J4.2 (SWDIO), U4.23 (SWDIO/!RESET)
TOBLE_TX: U4.47 (P28); also elsewhere on the board
V+: C11.1, C24.1, J4.1 (VCC), Q1.P3 (D), U4.1 (VDD), U4.12 (VDD)
VDD_PA: B1.VCC (VDD_PA), C22.1, U4.30 (VDD_PA)

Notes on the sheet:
PIN12
PIN1
PIN36

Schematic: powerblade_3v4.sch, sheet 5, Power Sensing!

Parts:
C2: 0.1uF; C0402; DIGIKEY 490-10777-1-ND
C13: 0.1uF; 0402_CAP; DIGIKEY 445-4952-1-ND
C27, C38: 0.1uF; C0402; DIGIKEY 445-4952-1-ND
C39: 1.5uF; C0402; DIGIKEY 445-13815-1-ND
L3: L-USL0805; L0805; DIGIKEY 732-3452-1-ND
Q4: 2SK1829; SC-70-3
R2: 3k; R0402_SM; DIGIKEY P3.00KLCT-ND
R6: 660k; R0402; DIGIKEY P665KLCT-ND
R14: 200; R0402; DIGIKEY P200LCT-ND
R15, R20, R40: 1M 1%; R0402; DIGIKEY P1.00MLCT-ND
R16: 75 1%; R0402; DIGIKEY P75.0LCT-ND
R17: 1k 1%; R0402; DIGIKEY P1.00KLCT-ND
R18: 4.99 1%; R0402; DIGIKEY RMCF0402FT4R99CT-ND
R21: 1M 1%; R0402_SM; DIGIKEY P1.00MLCT-ND
R35: 20k; R0402; DIGIKEY P20.0KLCT-ND
R37: 887k 1%; R0402; DIGIKEY P887KLCT-ND
R38: 30k 1%; R0402; DIGIKEY P30.0KLCT-ND
R39: 16k 1%; R0402; DIGIKEY P16.0KLCT-ND
RF: 4.99k 1%; R0402; DIGIKEY P4.99KLCT-ND
RI1, RI2: 953k 1%; R0402; DIGIKEY P953KLCT-ND
U2: MCP6V3; SC70-5; DIGIKEY 296-19547-1-ND
U6: MAX9910; SC70-5; DIGIKEY 296-25252-1-ND
U7: OPA2369; SOT-23-8

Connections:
+3V3: C13.1, C27.1, C38.1, R15.1, R20.2, R40.2, U2.P5 (VCC), U6.P5 (VCC), U7.P8 (VCC); also elsewhere on the board
METER_ENABLE: Q4.P1 (G), R6.1; also elsewhere on the board
unnamed: R2.1, R37.2, U7.P7 (OUT)
unnamed 20: L3.2, R14.1, R15.2, R16.2; also elsewhere on the board
unnamed: L3.1, R14.2, U2.P1 (IN+)
unnamed: R20.1, R21.2, U6.P1 (IN+)
unnamed: RF.1, RI1.2, RI2.2, U6.P3 (IN-)
unnamed 25: R17.1, R18.2, U2.P3 (IN-); also elsewhere on the board
unnamed: R37.1, R38.2, U7.P6 (IN-)
unnamed: R35.1, U7.P1 (OUT), U7.P2 (IN-)
unnamed: R39.2, R40.1, U7.P3 (IN+)
VAMP: C39.1, R17.2, U2.P4 (OUT)
VFILT: C39.2, R35.2, U7.P5 (IN+); also elsewhere on the board
VTEST: RI1.1; also elsewhere on the board

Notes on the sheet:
Voltage offset
50uV offset
For zero offset:
R15=NP
R16=0
Current Measurement
Voltage Measurement
Output voltage:
-(RF/RI)*VTEST + VCC/2
R15=1M
R16=15

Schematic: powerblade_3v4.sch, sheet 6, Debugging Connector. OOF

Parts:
SV1: MA12-11M27; MA12-1_1MM27; DIGIKEY S9014E-12-ND

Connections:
+3V3: SV1.P8 (8); also elsewhere on the board
FROMBLE_RX: SV1.P2 (2); also elsewhere on the board
PWM_CURRENT: SV1.P5 (5); also elsewhere on the board
PWM_VOLTAGE: SV1.P4 (4); also elsewhere on the board
TOBLE_TX: SV1.P1 (1); also elsewhere on the board
VCC: SV1.P10 (10); also elsewhere on the board
VFILT: SV1.P9 (9); also elsewhere on the board
VS+: SV1.P12 (12); also elsewhere on the board
ZC: SV1.P11 (11); also elsewhere on the board

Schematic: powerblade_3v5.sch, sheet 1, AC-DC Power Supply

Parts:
C1: 33uF; CPOL0805_SM; DIGIKEY 478-8650-1-ND
C3: 22uF; C0603_SM; DIGIKEY 445-9077-1-ND
D1: ZENERBZT52; BZT52; DIGIKEY BZT52C10T-7DICT-ND
D2: DIODE; BAS521
J2: AC_INFINAL; AC3_FINAL; DIGIKEY ED1649-ND
R3: 69.8k; R1210; DIGIKEY P69.8KAACT-ND

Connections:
VCC: C1.+, C3.1, D2.C; also elsewhere on the board
VTEST: J2.PA.3, R3.1; also elsewhere on the board
ZC: D1.C, D2.A, R3.2; also elsewhere on the board

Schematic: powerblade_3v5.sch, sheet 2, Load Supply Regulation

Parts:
C4: 22pF; C0402; DIGIKEY 445-1239-1-ND
C5: NP; C0603_TN; DIGIKEY NP
C7: 4.7uF; C0402; DIGIKEY 445-8023-1-ND
C8: 0.1uF; C0402; DIGIKEY 445-4952-1-ND
C9: 0.1uF; C0402_SM; DIGIKEY 445-4952-1-ND
C10: 22uF; C0603_SM; DIGIKEY 445-9077-1-ND
L1: 10uH; L0805; DIGIKEY 490-4990-1-ND
R7: 560k; R0402; DIGIKEY P560KLCT-ND
R9: 180k; R0402; DIGIKEY P180KLCT-ND
R24: 1 1%; R0603_SM; DIGIKEY P1.0AJCT-ND
U1: TPS62122; WDFN-6

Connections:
+3V3: C5.1, R24.2; also elsewhere on the board
unnamed: L1.2, U1.P1 (SW)
unnamed: C4.2, R7.1, R9.2, U1.P3 (FB)
VCC: C7.1, C8.1, U1.P4 (EN), U1.P5 (VIN); also elsewhere on the board
VS+: C4.1, C9.1, C10.1, L1.1, R7.2, R24.1, U1.P2 (VOUT); also elsewhere on the board

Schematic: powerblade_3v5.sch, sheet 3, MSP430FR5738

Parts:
C6, C34: 8pF; C0402; DIGIKEY 445-4890-1-ND
C14: 0.1uF; C0402; DIGIKEY 445-4952-1-ND
C15: 10uF; C0603_SM; DIGIKEY 445-6853-1-ND
C16: 470nF; C0402; DIGIKEY 445-4989-1-ND
J1: JTAG_14PIN_IDC-ND; TC2050-IDC-NL-430-ND; DIGIKEY NP
R11, R22: 670k; R0402; DIGIKEY P665KLCT-ND
R12, R13: 330k; R0402; DIGIKEY P330KLCT-ND
R19: 47k; R0402; DIGIKEY P47KJCT-ND
U3: MSP430FR5738; VQFN-24
X3: 32.768kHz; 0805; DIGIKEY 535-12373-1-ND

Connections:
+3V3: C14.1, C15.1, J1.P2 (2), R19.2, U3.P20 (DVCC), U3.P24 (AVCC); also elsewhere on the board
BLE_ENABLE: U3.P16 (P1.6/TA0.0/UCBSDA/MOSI); also elsewhere on the board
BLE_LPINT: U3.P17 (P1.7/TA1.0/UCBSCL/MISO); also elsewhere on the board
FROMBLE_RX: U3.P14 (P2.1/TB0.0/UCARX/MISO); also elsewhere on the board
METER_ENABLE: U3.P15 (P2.2/UCBCLK); also elsewhere on the board
unnamed: C34.2, U3.P22 (XOUT), X3.1
unnamed: C16.2, U3.P18 (VCORE)
unnamed: C6.2, U3.P21 (XIN), X3.2
PWM_CURRENT: U3.P3 (P1.2/TA1.1/A2); also elsewhere on the board
PWM_VOLTAGE: U3.P4 (P1.3/TA1.2/A3); also elsewhere on the board
RST: J1.P10 (11), R19.1, U3.P12 (RST)
TCK: J1.P7 (7), U3.P10 (TCK)
TDI: J1.P3 (3), U3.P8 (TDI)
TDO: J1.P1 (1), R13.2, R22.1, U3.P7 (TDO)
TEST: J1.P8 (8), U3.P11 (TEST)
TMS: J1.P5 (5), U3.P9 (TMS)
TOBLE_TX: U3.P13 (P2.0/UCATX/MOSI); also elsewhere on the board
VCC: R11.2; also elsewhere on the board
VCC_SENSE: R11.1, R12.2, U3.P6 (P1.5/TB0.2/UCACLK)
VFILT: U3.P2 (P1.1/VREF+); also elsewhere on the board
ZC: R22.2; also elsewhere on the board
